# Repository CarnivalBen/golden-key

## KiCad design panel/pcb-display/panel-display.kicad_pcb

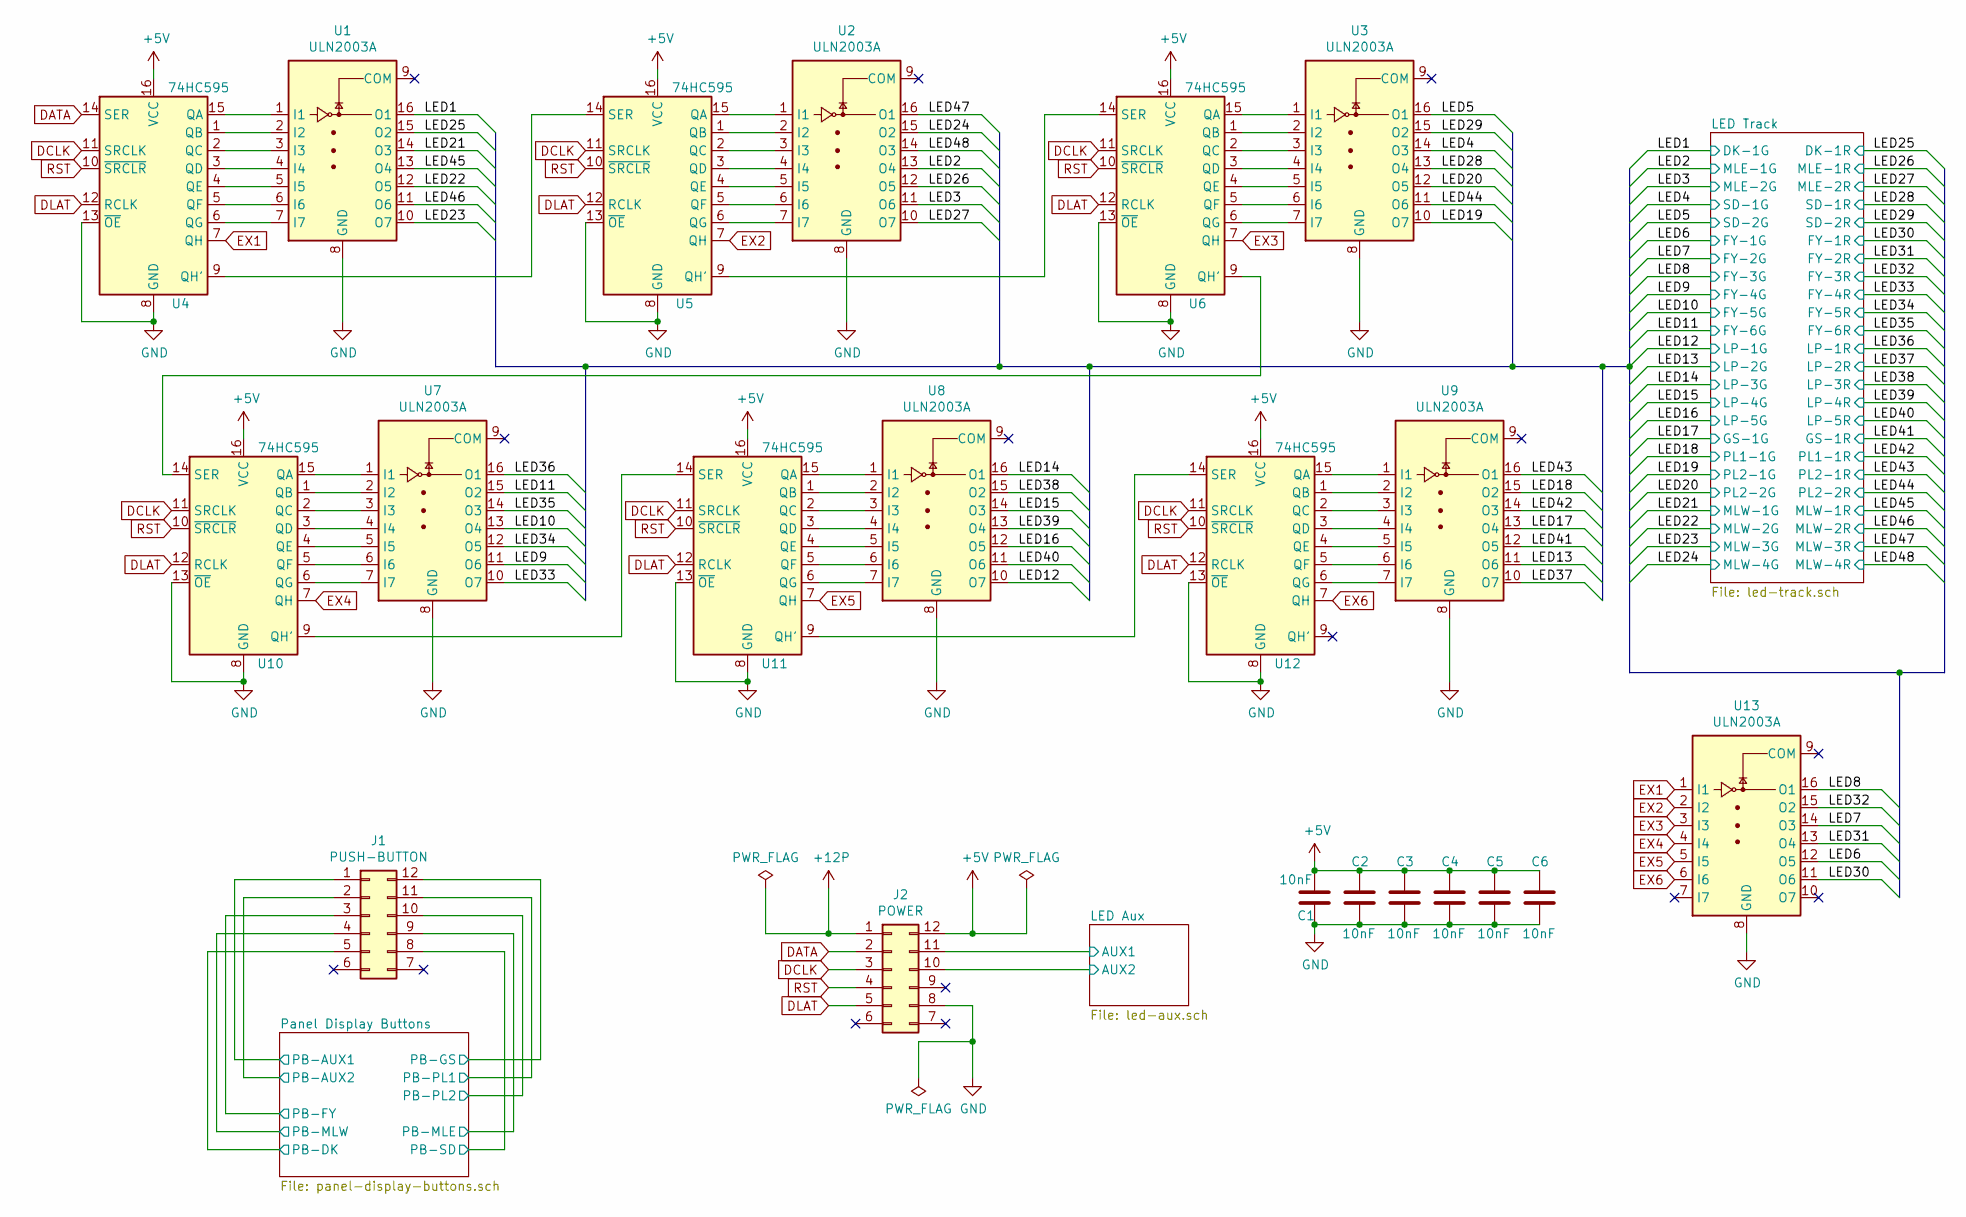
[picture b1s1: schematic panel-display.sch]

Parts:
C1, C2, C3, C4, C5, C6: 10nF; C_Disc_D3.0mm_W1.6mm_P2.50mm
J1: PUSH-BUTTON; Pin_Header_Straight_2x06_Pitch2.54mm
J2: POWER; Pin_Header_Straight_2x06_Pitch2.54mm
U1, U2, U3, U7, U8, U9, U13: ULN2003A; DIP-16_W7.62mm_LongPads
U4, U5, U6, U10, U11, U12: 74HC595; DIP-16_W7.62mm_LongPads

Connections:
+5V: C1.2, C2.2, C3.2, C4.2, C5.2, C6.2, J2.12, U4.16 (VCC), U5.16 (VCC), U6.16 (VCC), U10.16 (VCC), U11.16 (VCC), U12.16 (VCC); also elsewhere on the board
+12P: J2.1; also elsewhere on the board
/LED1: U1.16 (O1); also elsewhere on the board
/LED2: U2.13 (O4); also elsewhere on the board
/LED3: U2.11 (O6); also elsewhere on the board
/LED4: U3.14 (O3); also elsewhere on the board
/LED5: U3.16 (O1); also elsewhere on the board
/LED6: U13.12 (O5); also elsewhere on the board
/LED7: U13.14 (O3); also elsewhere on the board
/LED8: U13.16 (O1); also elsewhere on the board
/LED9: U7.11 (O6); also elsewhere on the board
/LED10: U7.13 (O4); also elsewhere on the board
/LED11: U7.15 (O2); also elsewhere on the board
/LED12: U8.10 (O7); also elsewhere on the board
/LED13: U9.11 (O6); also elsewhere on the board
/LED14: U8.16 (O1); also elsewhere on the board
/LED15: U8.14 (O3); also elsewhere on the board
/LED16: U8.12 (O5); also elsewhere on the board
/LED17: U9.13 (O4); also elsewhere on the board
/LED18: U9.15 (O2); also elsewhere on the board
/LED19: U3.10 (O7); also elsewhere on the board
/LED20: U3.12 (O5); also elsewhere on the board
/LED21: U1.14 (O3); also elsewhere on the board
/LED22: U1.12 (O5); also elsewhere on the board
/LED23: U1.10 (O7); also elsewhere on the board
/LED24: U2.15 (O2); also elsewhere on the board
/LED25: U1.15 (O2); also elsewhere on the board
/LED26: U2.12 (O5); also elsewhere on the board
/LED27: U2.10 (O7); also elsewhere on the board
/LED28: U3.13 (O4); also elsewhere on the board
/LED29: U3.15 (O2); also elsewhere on the board
/LED30: U13.11 (O6); also elsewhere on the board
/LED31: U13.13 (O4); also elsewhere on the board
/LED32: U13.15 (O2); also elsewhere on the board
/LED33: U7.10 (O7); also elsewhere on the board
/LED34: U7.12 (O5); also elsewhere on the board
/LED35: U7.14 (O3); also elsewhere on the board
/LED36: U7.16 (O1); also elsewhere on the board
/LED37: U9.10 (O7); also elsewhere on the board
/LED38: U8.15 (O2); also elsewhere on the board
/LED39: U8.13 (O4); also elsewhere on the board
/LED40: U8.11 (O6); also elsewhere on the board
/LED41: U9.12 (O5); also elsewhere on the board
/LED42: U9.14 (O3); also elsewhere on the board
/LED43: U9.16 (O1); also elsewhere on the board
/LED44: U3.11 (O6); also elsewhere on the board
/LED45: U1.13 (O4); also elsewhere on the board
/LED46: U1.11 (O6); also elsewhere on the board
/LED47: U2.16 (O1); also elsewhere on the board
/LED48: U2.14 (O3); also elsewhere on the board
/LED Aux/AUX1: J2.11; also elsewhere on the board
/LED Aux/AUX2: J2.10; also elsewhere on the board
/Panel Display Buttons/PB-AUX1: J1.1; also elsewhere on the board
/Panel Display Buttons/PB-AUX2: J1.2; also elsewhere on the board
/Panel Display Buttons/PB-DK: J1.5; also elsewhere on the board
/Panel Display Buttons/PB-FY: J1.3; also elsewhere on the board
/Panel Display Buttons/PB-GS: J1.12; also elsewhere on the board
/Panel Display Buttons/PB-MLE: J1.9; also elsewhere on the board
/Panel Display Buttons/PB-MLW: J1.4; also elsewhere on the board
/Panel Display Buttons/PB-PL1: J1.11; also elsewhere on the board
/Panel Display Buttons/PB-PL2: J1.10; also elsewhere on the board
/Panel Display Buttons/PB-SD: J1.8; also elsewhere on the board
DATA: J2.2, U4.14 (SER)
DCLK: J2.3, U4.11 (SRCLK), U5.11 (SRCLK), U6.11 (SRCLK), U10.11 (SRCLK), U11.11 (SRCLK), U12.11 (SRCLK)
DLAT: J2.5, U4.12 (RCLK), U5.12 (RCLK), U6.12 (RCLK), U10.12 (RCLK), U11.12 (RCLK), U12.12 (RCLK)
EX1: U4.7 (QH), U13.1 (I1)
EX2: U5.7 (QH), U13.2 (I2)
EX3: U6.7 (QH), U13.3 (I3)
EX4: U10.7 (QH), U13.4 (I4)
EX5: U11.7 (QH), U13.5 (I5)
EX6: U12.7 (QH), U13.6 (I6)
GND: C1.1, C2.1, C3.1, C4.1, C5.1, C6.1, J2.8, U1.8 (GND), U2.8 (GND), U3.8 (GND), U4.8 (GND), U4.13 (~OE), U5.8 (GND), U5.13 (~OE), U6.8 (GND), U6.13 (~OE), U7.8 (GND), U8.8 (GND), U9.8 (GND), U10.8 (GND), U10.13 (~OE), U11.8 (GND), U11.13 (~OE), U12.8 (GND), U12.13 (~OE), U13.8 (GND); also elsewhere on the board
unnamed: U1.1 (I1), U4.15 (QA)
unnamed: U1.2 (I2), U4.1 (QB)
unnamed: U1.3 (I3), U4.2 (QC)
unnamed: U1.4 (I4), U4.3 (QD)
unnamed: U1.5 (I5), U4.4 (QE)
unnamed: U1.6 (I6), U4.5 (QF)
unnamed: U1.7 (I7), U4.6 (QG)
unnamed: U2.1 (I1), U5.15 (QA)
unnamed: U2.2 (I2), U5.1 (QB)
unnamed: U2.3 (I3), U5.2 (QC)
unnamed: U2.4 (I4), U5.3 (QD)
unnamed: U2.5 (I5), U5.4 (QE)
unnamed: U2.6 (I6), U5.5 (QF)
unnamed: U2.7 (I7), U5.6 (QG)
unnamed: U3.1 (I1), U6.15 (QA)
unnamed: U3.2 (I2), U6.1 (QB)
unnamed: U3.3 (I3), U6.2 (QC)
unnamed: U3.4 (I4), U6.3 (QD)
unnamed: U3.5 (I5), U6.4 (QE)
unnamed: U3.6 (I6), U6.5 (QF)
unnamed: U3.7 (I7), U6.6 (QG)
unnamed: U4.9 (QH'), U5.14 (SER)
unnamed: U5.9 (QH'), U6.14 (SER)
unnamed: U7.2 (I2), U10.1 (QB)
unnamed: U7.3 (I3), U10.2 (QC)
unnamed: U7.4 (I4), U10.3 (QD)
unnamed: U7.5 (I5), U10.4 (QE)
unnamed: U7.6 (I6), U10.5 (QF)
unnamed: U7.7 (I7), U10.6 (QG)
unnamed: U10.9 (QH'), U11.14 (SER)
unnamed: U6.9 (QH'), U10.14 (SER)
unnamed: U7.1 (I1), U10.15 (QA)
unnamed: U8.2 (I2), U11.1 (QB)
unnamed: U8.3 (I3), U11.2 (QC)
unnamed: U8.4 (I4), U11.3 (QD)
unnamed: U8.5 (I5), U11.4 (QE)
unnamed: U8.6 (I6), U11.5 (QF)
unnamed: U8.7 (I7), U11.6 (QG)
unnamed: U11.9 (QH'), U12.14 (SER)
unnamed: U8.1 (I1), U11.15 (QA)
unnamed: U9.2 (I2), U12.1 (QB)
unnamed: U9.3 (I3), U12.2 (QC)
unnamed: U9.4 (I4), U12.3 (QD)
unnamed: U9.5 (I5), U12.4 (QE)
unnamed: U9.6 (I6), U12.5 (QF)
unnamed: U9.7 (I7), U12.6 (QG)
unnamed: U9.1 (I1), U12.15 (QA)
RST: J2.4, U4.10 (~SRCLR), U5.10 (~SRCLR), U6.10 (~SRCLR), U10.10 (~SRCLR), U11.10 (~SRCLR), U12.10 (~SRCLR)

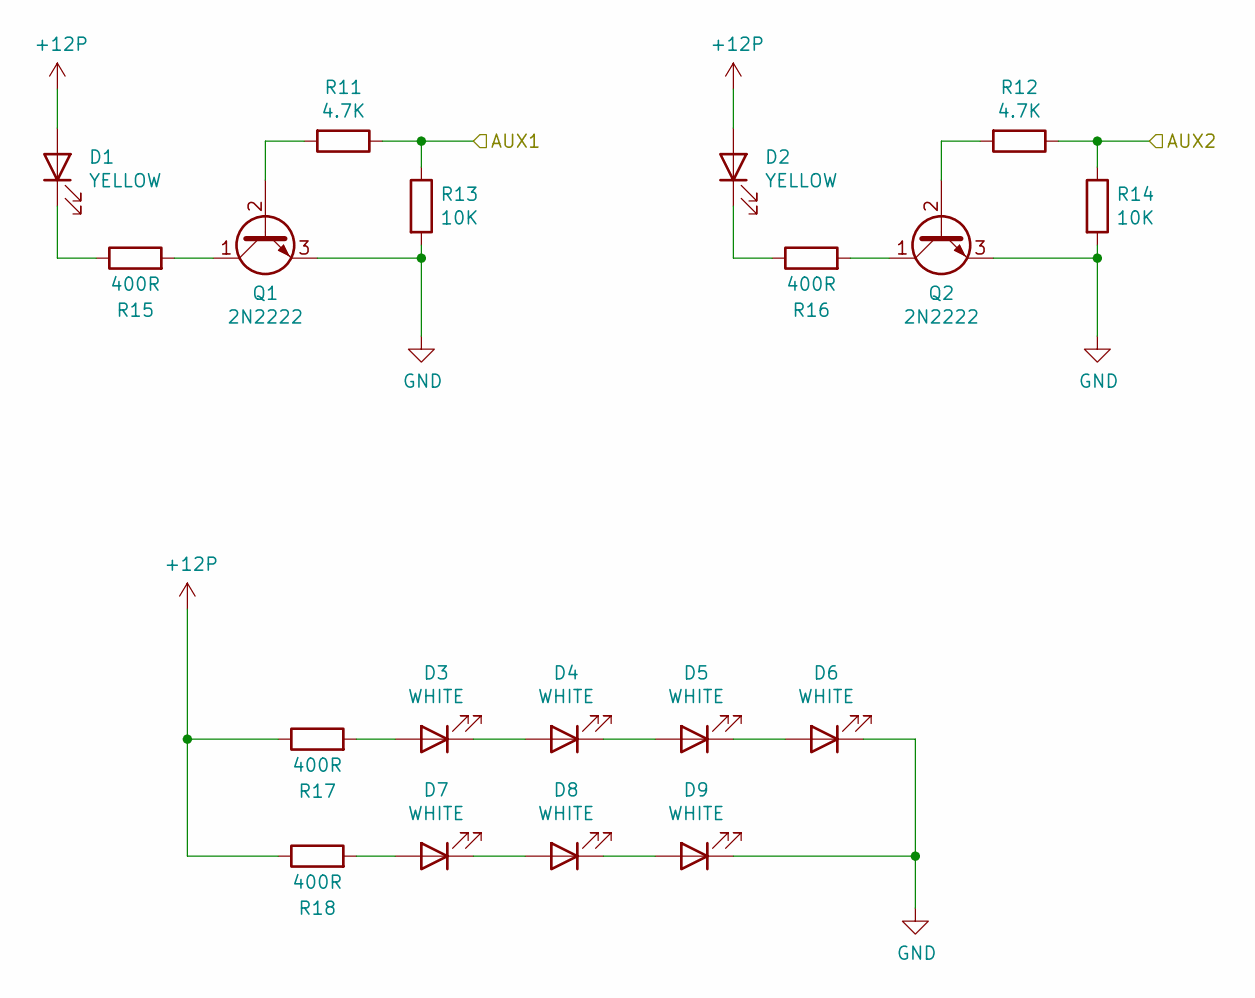
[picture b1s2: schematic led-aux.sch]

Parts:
D1, D2: YELLOW; LED_D5.0mm
D3, D4, D5, D6, D7, D8, D9: WHITE; LED_D5.0mm
Q1, Q2: 2N2222; TO-92_Inline_Wide
R11, R12: 4.7K; R_Axial_DIN0207_L6.3mm_D2.5mm_P10.16mm_Horizontal
R13, R14: 10K; R_Axial_DIN0207_L6.3mm_D2.5mm_P10.16mm_Horizontal
R15, R16, R17, R18: 400R; R_Axial_DIN0207_L6.3mm_D2.5mm_P10.16mm_Horizontal

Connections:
+12P: D1.2 (A), D2.2 (A), R17.1, R18.1; also elsewhere on the board
/LED Aux/AUX1: R11.1, R13.1; also elsewhere on the board
/LED Aux/AUX2: R12.1, R14.1; also elsewhere on the board
GND: D6.1 (K), D9.1 (K), Q1.3 (E), Q2.3 (E), R13.2, R14.2; also elsewhere on the board
unnamed: D1.1 (K), R15.1
unnamed: D2.1 (K), R16.1
unnamed: D3.1 (K), D4.2 (A)
unnamed: D3.2 (A), R17.2
unnamed: D4.1 (K), D5.2 (A)
unnamed: D5.1 (K), D6.2 (A)
unnamed: D7.1 (K), D8.2 (A)
unnamed: D7.2 (A), R18.2
unnamed: D8.1 (K), D9.2 (A)
unnamed: Q1.1 (C), R15.2
unnamed: Q1.2 (B), R11.2
unnamed: Q2.1 (C), R16.2
unnamed: Q2.2 (B), R12.2

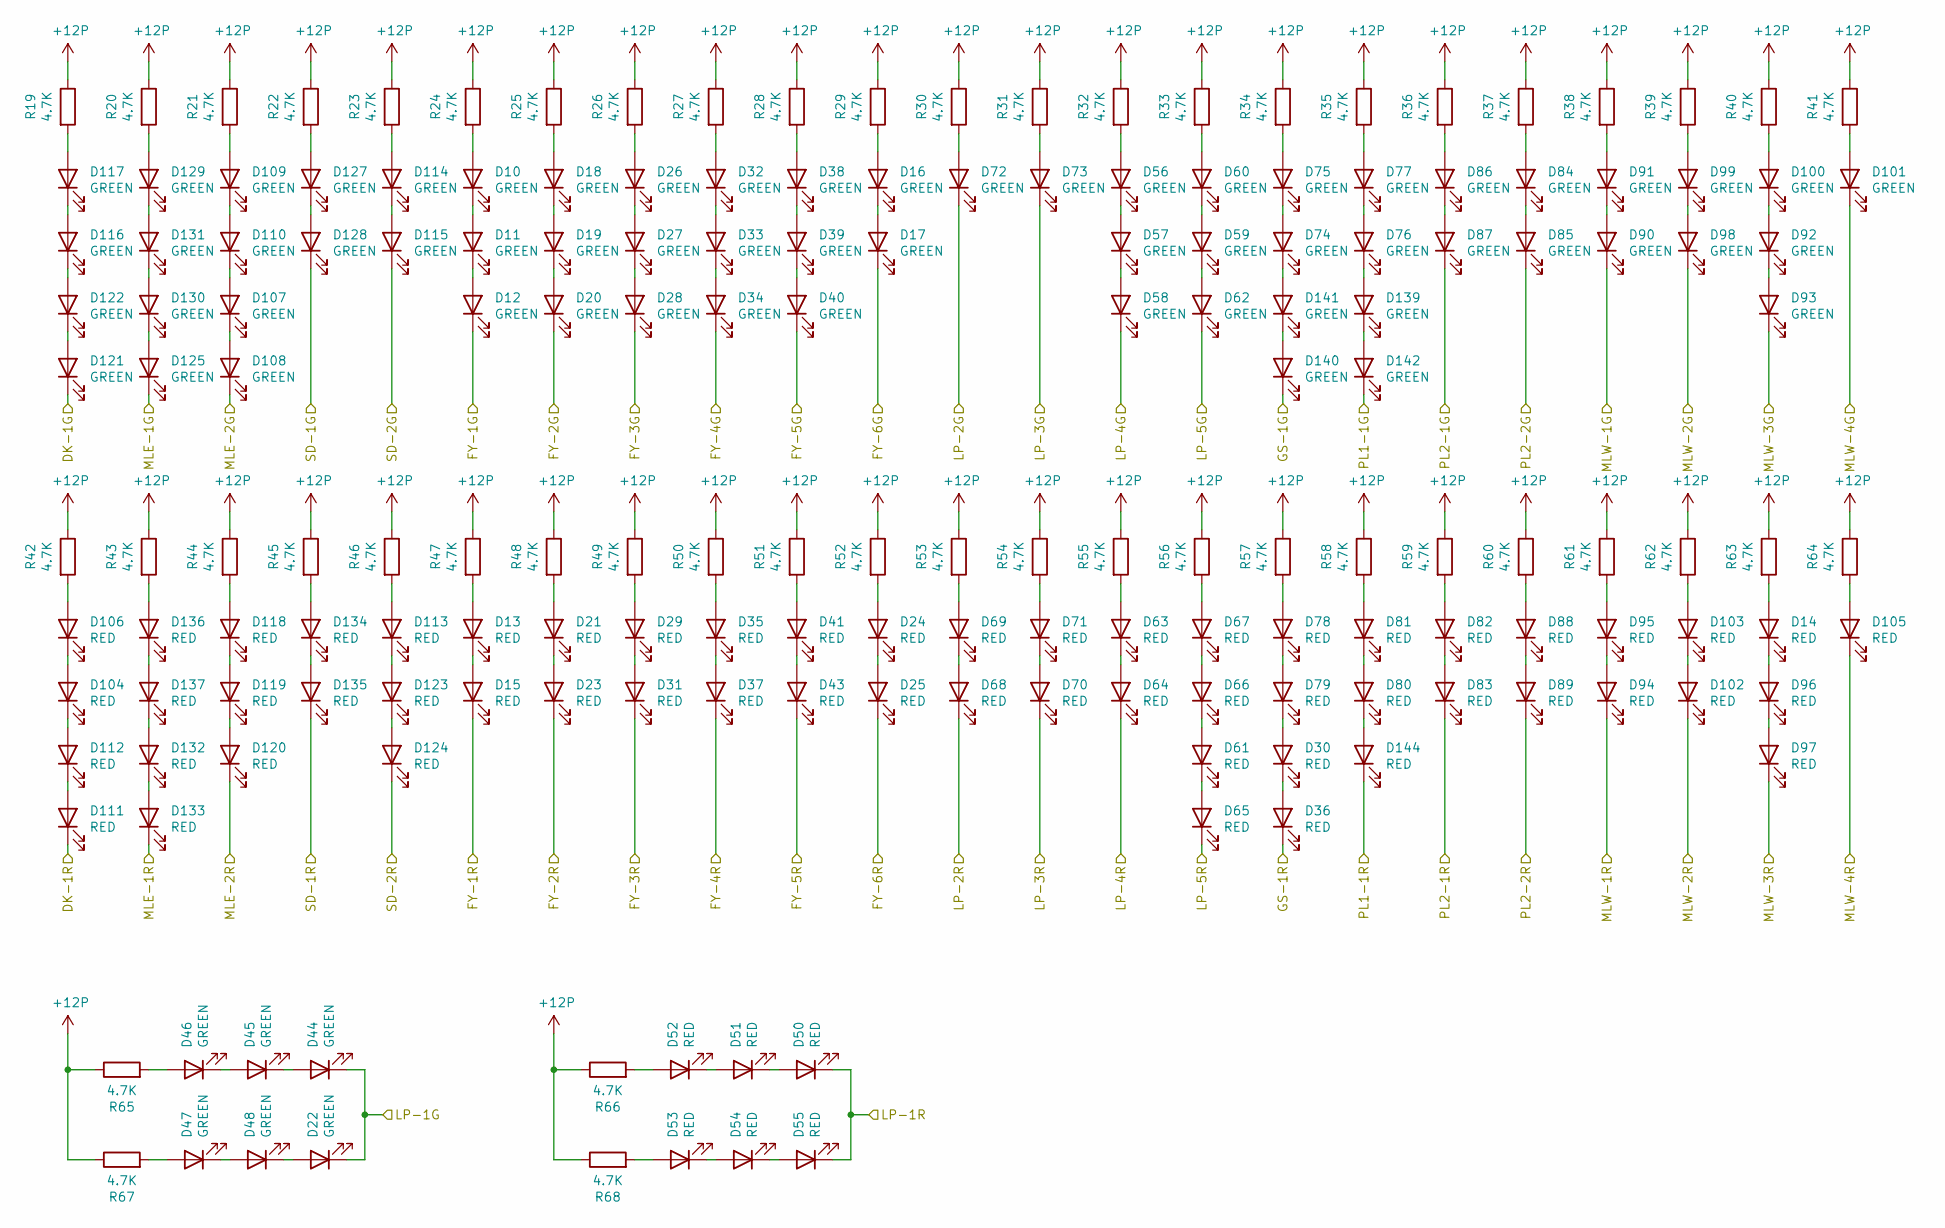
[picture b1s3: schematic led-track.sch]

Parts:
D10, D11, D12, D16, D17, D18, D19, D20, D22, D26, D27, D28, D32, D33, D34, D38, D39, D40, D44, D45, D46, D47, D48, D56, D57, D58, D59, D60, D62, D72, D73, D74, D75, D76, D77, D84, D85, D86, D87, D90, D91, D92, D93, D98, D99, D100, D101, D107, D108, D109, D110, D114, D115, D116, D117, D121, D122, D125, D127, D128, D129, D130, D131, D139, D140, D141, D142: GREEN; LED_D5.0mm
D13, D14, D15, D21, D23, D24, D25, D29, D30, D31, D35, D36, D37, D41, D43, D50, D51, D52, D53, D54, D55, D61, D63, D64, D65, D66, D67, D68, D69, D70, D71, D78, D79, D80, D81, D82, D83, D88, D89, D94, D95, D96, D97, D102, D103, D104, D105, D106, D111, D112, D113, D118, D119, D120, D123, D124, D132, D133, D134, D135, D136, D137, D144: RED; LED_D5.0mm
R19, R20, R21, R22, R23, R24, R25, R26, R27, R28, R29, R30, R31, R32, R33, R34, R35, R36, R37, R38, R39, R40, R41, R42, R43, R44, R45, R46, R47, R48, R49, R50, R51, R52, R53, R54, R55, R56, R57, R58, R59, R60, R61, R62, R63, R64, R65, R66, R67, R68: 4.7K; R_Axial_DIN0207_L6.3mm_D2.5mm_P10.16mm_Horizontal

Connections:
+12P: R19.1, R20.1, R21.1, R22.1, R23.1, R24.1, R25.1, R26.1, R27.1, R28.1, R29.1, R30.1, R31.1, R32.1, R33.1, R34.1, R35.1, R36.1, R37.1, R38.1, R39.1, R40.1, R41.1, R42.1, R43.1, R44.1, R45.1, R46.1, R47.1, R48.1, R49.1, R50.1, R51.1, R52.1, R53.1, R54.1, R55.1, R56.1, R57.1, R58.1, R59.1, R60.1, R61.1, R62.1, R63.1, R64.1, R65.1, R66.1, R67.1, R68.1; also elsewhere on the board
/LED1: D121.1 (K); also elsewhere on the board
/LED2: D125.1 (K); also elsewhere on the board
/LED3: D108.1 (K); also elsewhere on the board
/LED4: D128.1 (K); also elsewhere on the board
/LED5: D115.1 (K); also elsewhere on the board
/LED6: D12.1 (K); also elsewhere on the board
/LED7: D20.1 (K); also elsewhere on the board
/LED8: D28.1 (K); also elsewhere on the board
/LED9: D34.1 (K); also elsewhere on the board
/LED10: D40.1 (K); also elsewhere on the board
/LED11: D17.1 (K); also elsewhere on the board
/LED12: D22.1 (K), D44.1 (K); also elsewhere on the board
/LED13: D72.1 (K); also elsewhere on the board
/LED14: D73.1 (K); also elsewhere on the board
/LED15: D58.1 (K); also elsewhere on the board
/LED16: D62.1 (K); also elsewhere on the board
/LED17: D140.1 (K); also elsewhere on the board
/LED18: D142.1 (K); also elsewhere on the board
/LED19: D87.1 (K); also elsewhere on the board
/LED20: D85.1 (K); also elsewhere on the board
/LED21: D90.1 (K); also elsewhere on the board
/LED22: D98.1 (K); also elsewhere on the board
/LED23: D93.1 (K); also elsewhere on the board
/LED24: D101.1 (K); also elsewhere on the board
/LED25: D111.1 (K); also elsewhere on the board
/LED26: D133.1 (K); also elsewhere on the board
/LED27: D120.1 (K); also elsewhere on the board
/LED28: D135.1 (K); also elsewhere on the board
/LED29: D124.1 (K); also elsewhere on the board
/LED30: D15.1 (K); also elsewhere on the board
/LED31: D23.1 (K); also elsewhere on the board
/LED32: D31.1 (K); also elsewhere on the board
/LED33: D37.1 (K); also elsewhere on the board
/LED34: D43.1 (K); also elsewhere on the board
/LED35: D25.1 (K); also elsewhere on the board
/LED36: D50.1 (K), D55.1 (K); also elsewhere on the board
/LED37: D68.1 (K); also elsewhere on the board
/LED38: D70.1 (K); also elsewhere on the board
/LED39: D64.1 (K); also elsewhere on the board
/LED40: D65.1 (K); also elsewhere on the board
/LED41: D36.1 (K); also elsewhere on the board
/LED42: D144.1 (K); also elsewhere on the board
/LED43: D83.1 (K); also elsewhere on the board
/LED44: D89.1 (K); also elsewhere on the board
/LED45: D94.1 (K); also elsewhere on the board
/LED46: D102.1 (K); also elsewhere on the board
/LED47: D97.1 (K); also elsewhere on the board
/LED48: D105.1 (K); also elsewhere on the board
unnamed: D10.1 (K), D11.2 (A)
unnamed: D10.2 (A), R24.2
unnamed: D11.1 (K), D12.2 (A)
unnamed: D13.1 (K), D15.2 (A)
unnamed: D13.2 (A), R47.2
unnamed: D14.1 (K), D96.2 (A)
unnamed: D14.2 (A), R63.2
unnamed: D16.1 (K), D17.2 (A)
unnamed: D16.2 (A), R29.2
unnamed: D18.1 (K), D19.2 (A)
unnamed: D18.2 (A), R25.2
unnamed: D19.1 (K), D20.2 (A)
unnamed: D21.1 (K), D23.2 (A)
unnamed: D21.2 (A), R48.2
unnamed: D22.2 (A), D48.1 (K)
unnamed: D24.1 (K), D25.2 (A)
unnamed: D24.2 (A), R52.2
unnamed: D26.1 (K), D27.2 (A)
unnamed: D26.2 (A), R26.2
unnamed: D27.1 (K), D28.2 (A)
unnamed: D29.1 (K), D31.2 (A)
unnamed: D29.2 (A), R49.2
unnamed: D30.1 (K), D36.2 (A)
unnamed: D30.2 (A), D79.1 (K)
unnamed: D32.1 (K), D33.2 (A)
unnamed: D32.2 (A), R27.2
unnamed: D33.1 (K), D34.2 (A)
unnamed: D35.1 (K), D37.2 (A)
unnamed: D35.2 (A), R50.2
unnamed: D38.1 (K), D39.2 (A)
unnamed: D38.2 (A), R28.2
unnamed: D39.1 (K), D40.2 (A)
unnamed: D41.1 (K), D43.2 (A)
unnamed: D41.2 (A), R51.2
unnamed: D44.2 (A), D45.1 (K)
unnamed: D45.2 (A), D46.1 (K)
unnamed: D46.2 (A), R65.2
unnamed: D47.1 (K), D48.2 (A)
unnamed: D47.2 (A), R67.2
unnamed: D50.2 (A), D51.1 (K)
unnamed: D51.2 (A), D52.1 (K)
unnamed: D52.2 (A), R66.2
unnamed: D53.1 (K), D54.2 (A)
unnamed: D53.2 (A), R68.2
unnamed: D54.1 (K), D55.2 (A)
unnamed: D56.1 (K), D57.2 (A)
unnamed: D56.2 (A), R32.2
unnamed: D57.1 (K), D58.2 (A)
unnamed: D59.1 (K), D62.2 (A)
unnamed: D59.2 (A), D60.1 (K)
unnamed: D60.2 (A), R33.2
unnamed: D61.1 (K), D65.2 (A)
unnamed: D61.2 (A), D66.1 (K)
unnamed: D63.1 (K), D64.2 (A)
unnamed: D63.2 (A), R55.2
unnamed: D66.2 (A), D67.1 (K)
unnamed: D67.2 (A), R56.2
unnamed: D68.2 (A), D69.1 (K)
unnamed: D69.2 (A), R53.2
unnamed: D70.2 (A), D71.1 (K)
unnamed: D71.2 (A), R54.2
unnamed: D72.2 (A), R30.2
unnamed: D73.2 (A), R31.2
unnamed: D74.2 (A), D75.1 (K)
unnamed: D75.2 (A), R34.2
unnamed: D76.2 (A), D77.1 (K)
unnamed: D77.2 (A), R35.2
unnamed: D78.1 (K), D79.2 (A)
unnamed: D78.2 (A), R57.2
unnamed: D80.2 (A), D81.1 (K)
unnamed: D81.2 (A), R58.2
unnamed: D82.1 (K), D83.2 (A)
unnamed: D82.2 (A), R59.2
unnamed: D84.1 (K), D85.2 (A)
unnamed: D84.2 (A), R37.2
unnamed: D86.1 (K), D87.2 (A)
unnamed: D86.2 (A), R36.2
unnamed: D88.1 (K), D89.2 (A)
unnamed: D88.2 (A), R60.2
unnamed: D90.2 (A), D91.1 (K)
unnamed: D91.2 (A), R38.2
unnamed: D92.1 (K), D93.2 (A)
unnamed: D94.2 (A), D95.1 (K)
unnamed: D95.2 (A), R61.2
unnamed: D96.1 (K), D97.2 (A)
unnamed: D98.2 (A), D99.1 (K)
unnamed: D99.2 (A), R39.2
unnamed: D92.2 (A), D100.1 (K)
unnamed: D100.2 (A), R40.2
unnamed: D101.2 (A), R41.2
unnamed: D102.2 (A), D103.1 (K)
unnamed: D103.2 (A), R62.2
unnamed: D104.1 (K), D112.2 (A)
unnamed: D104.2 (A), D106.1 (K)
unnamed: D105.2 (A), R64.2
unnamed: D106.2 (A), R42.2
unnamed: D107.1 (K), D108.2 (A)
unnamed: D107.2 (A), D110.1 (K)
unnamed: D109.1 (K), D110.2 (A)
unnamed: D109.2 (A), R21.2
unnamed: D111.2 (A), D112.1 (K)
unnamed: D113.1 (K), D123.2 (A)
unnamed: D113.2 (A), R46.2
unnamed: D114.1 (K), D115.2 (A)
unnamed: D114.2 (A), R23.2
unnamed: D116.1 (K), D122.2 (A)
unnamed: D116.2 (A), D117.1 (K)
unnamed: D117.2 (A), R19.2
unnamed: D118.1 (K), D119.2 (A)
unnamed: D118.2 (A), R44.2
unnamed: D119.1 (K), D120.2 (A)
unnamed: D121.2 (A), D122.1 (K)
unnamed: D123.1 (K), D124.2 (A)
unnamed: D125.2 (A), D130.1 (K)
unnamed: D127.1 (K), D128.2 (A)
unnamed: D127.2 (A), R22.2
unnamed: D129.1 (K), D131.2 (A)
unnamed: D129.2 (A), R20.2
unnamed: D130.2 (A), D131.1 (K)
unnamed: D132.1 (K), D133.2 (A)
unnamed: D132.2 (A), D137.1 (K)
unnamed: D134.1 (K), D135.2 (A)
unnamed: D134.2 (A), R45.2
unnamed: D136.1 (K), D137.2 (A)
unnamed: D136.2 (A), R43.2
unnamed: D139.1 (K), D142.2 (A)
unnamed: D76.1 (K), D139.2 (A)
unnamed: D140.2 (A), D141.1 (K)
unnamed: D74.1 (K), D141.2 (A)
unnamed: D80.1 (K), D144.2 (A)

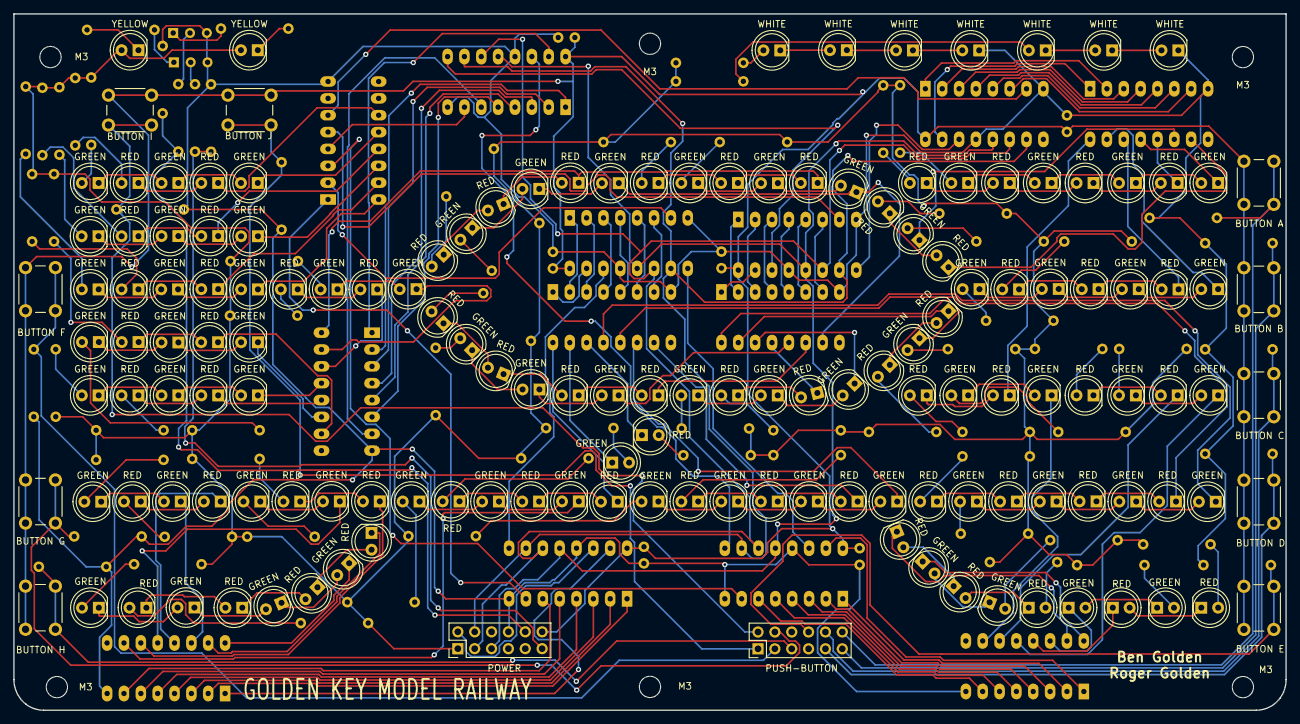
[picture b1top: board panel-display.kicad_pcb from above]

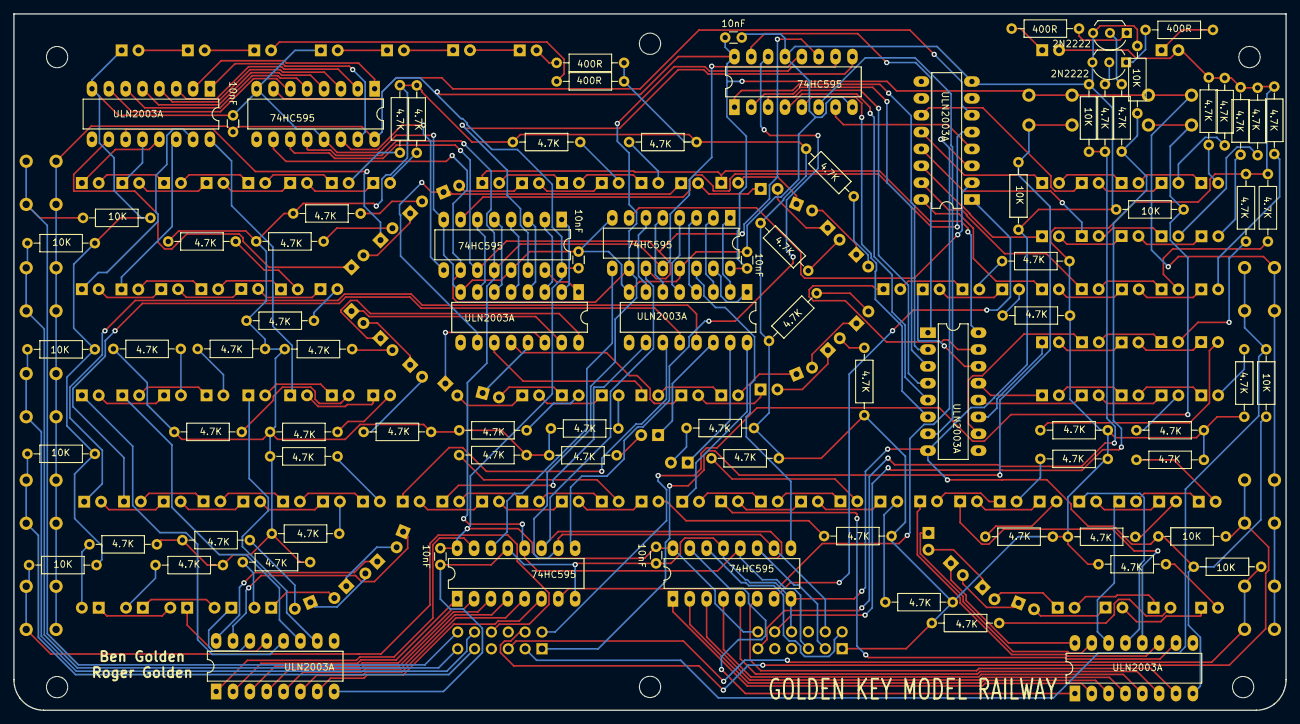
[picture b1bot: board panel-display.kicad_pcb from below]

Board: 2 copper layers, 191.7 x 104.9 mm, 240 parts (89 on the bottom side), 263 nets.

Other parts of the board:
R1, R2, R3, R4, R5, R6, R7, R8, R9, R10: 10K; R_Axial_DIN0207_L6.3mm_D2.5mm_P10.16mm_Horizontal
SW1: BUTTON J; SW_PUSH_6mm_4pin
SW2: BUTTON I; SW_PUSH_6mm_4pin
SW3: BUTTON F; SW_PUSH_6mm_4pin
SW4: BUTTON G; SW_PUSH_6mm_4pin
SW5: BUTTON H; SW_PUSH_6mm_4pin
SW6: BUTTON A; SW_PUSH_6mm_4pin
SW7: BUTTON B; SW_PUSH_6mm_4pin
SW8: BUTTON C; SW_PUSH_6mm_4pin
SW9: BUTTON D; SW_PUSH_6mm_4pin
SW10: BUTTON E; SW_PUSH_6mm_4pin

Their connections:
+5V: SW1.1, SW1.3, SW2.1, SW2.3, SW3.1, SW3.3, SW4.1, SW4.3, SW5.1, SW5.3, SW6.1, SW6.3, SW7.1, SW7.3, SW8.1, SW8.3, SW9.1, SW9.3, SW10.1, SW10.3; also elsewhere on the board
/Panel Display Buttons/PB-AUX1: R1.2, SW1.2, SW1.4; also elsewhere on the board
/Panel Display Buttons/PB-AUX2: R2.2, SW2.2, SW2.4; also elsewhere on the board
/Panel Display Buttons/PB-DK: R5.2, SW5.2, SW5.4; also elsewhere on the board
/Panel Display Buttons/PB-FY: R3.2, SW3.2, SW3.4; also elsewhere on the board
/Panel Display Buttons/PB-GS: R6.2, SW6.2, SW6.4; also elsewhere on the board
/Panel Display Buttons/PB-MLE: R9.2, SW9.2, SW9.4; also elsewhere on the board
/Panel Display Buttons/PB-MLW: R4.2, SW4.2, SW4.4; also elsewhere on the board
/Panel Display Buttons/PB-PL1: R7.2, SW7.2, SW7.4; also elsewhere on the board
/Panel Display Buttons/PB-PL2: R8.2, SW8.2, SW8.4; also elsewhere on the board
/Panel Display Buttons/PB-SD: R10.2, SW10.2, SW10.4; also elsewhere on the board
GND: R1.1, R2.1, R3.1, R4.1, R5.1, R6.1, R7.1, R8.1, R9.1, R10.1; also elsewhere on the board
